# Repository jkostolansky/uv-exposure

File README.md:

UV Exposure
===========

UV Exposure is a controller for a simple UV exposure unit for home PCB etching. It is written in Arduino programming language.

Repository Contents
-------------------

* **/schematics**
    * **/schematics/eagle** - Eagle schematics and PCB layout
    * **/schematics/images** - Images of schematics and PCB layout
* **/uv_exposure** - Arduino source code

The Beer-Ware License
---------------------

Juraj Kostolanský (@jkostolansky) wrote this file. As long as you retain this notice you can do whatever you want with this stuff. If we meet some day, and you think this stuff is worth it, you can buy me a beer in return.

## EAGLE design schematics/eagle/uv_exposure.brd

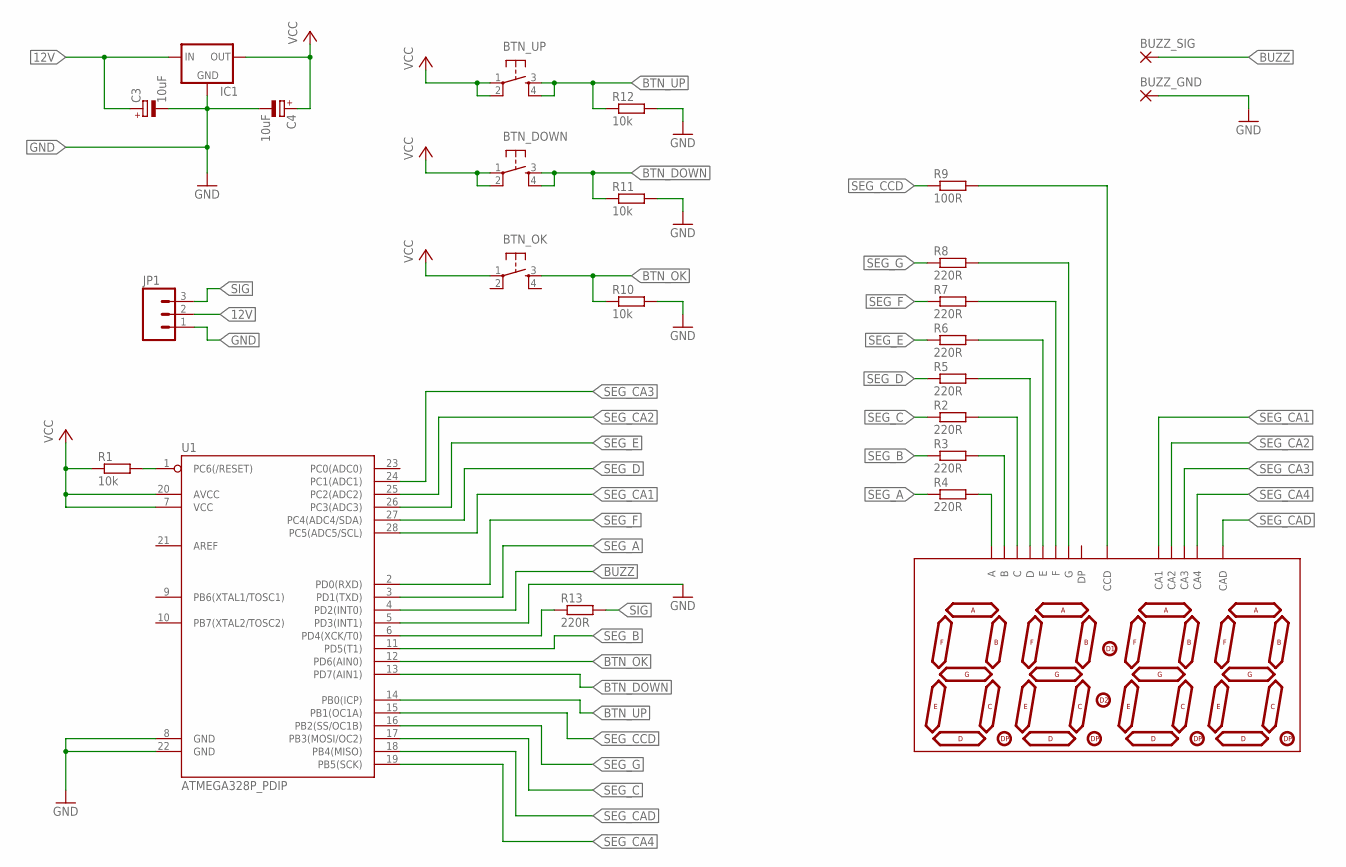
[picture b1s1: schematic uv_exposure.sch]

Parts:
BTN_DOWN: TAC_SWITCHPTH; TACTILE-PTH
BTN_OK: TAC_SWITCHPTH; TACTILE-PTH
BTN_UP: TAC_SWITCHPTH; TACTILE-PTH
BUZZ_GND: 2,54/0,8
BUZZ_SIG: 2,54/0,8
C3, C4: 10uF; E2-5
IC1: V_REG_78XXSINK; TO220-IGO
JP1: M03LOCK; 1X03_LOCK
R1, R10, R11, R12: 10k; 0207/10
R2, R3, R4, R5, R6, R7, R8, R13: 220R; 0207/10
R9: 100R; 0207/10
U1: ATMEGA328P_PDIP; DIL28-3
U$1: 5461BSDIP14; 5461BS

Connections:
12V: C3.+, IC1.IN, JP1.2
BTN_DOWN: BTN_DOWN.3, BTN_DOWN.4, R11.1, U1.13 (PD7(AIN1))
BTN_OK: BTN_OK.3, R10.1, U1.12 (PD6(AIN0))
BTN_UP: BTN_UP.3, BTN_UP.4, R12.1, U1.14 (PB0(ICP))
BUZZ: BUZZ_SIG.1, U1.4 (PD2(INT0))
GND: BUZZ_GND.1, C3.-, C4.-, IC1.GND, JP1.1, R10.2, R11.2, R12.2, U1.5 (PD3(INT1)), U1.8 (GND), U1.22 (GND)
unnamed: R1.2, U1.1 (PC6(/RESET))
unnamed: R4.2, U$1.13 (A)
unnamed: R3.2, U$1.9 (B)
unnamed: R2.2, U$1.4 (C)
unnamed: R5.2, U$1.2 (D)
unnamed: R6.2, U$1.1 (E)
unnamed: R7.2, U$1.12 (F)
unnamed: R8.2, U$1.5 (G)
unnamed: R9.2, U$1.8 (CCD)
unnamed: R13.1, U1.6 (PD4(XCK/T0))
SEG_A: R4.1, U1.3 (PD1(TXD))
SEG_B: R3.1, U1.11 (PD5(T1))
SEG_C: R2.1, U1.17 (PB3(MOSI/OC2))
SEG_CA1: U1.28 (PC5(ADC5/SCL)), U$1.14 (CA1)
SEG_CA2: U1.25 (PC2(ADC2)), U$1.11 (CA2)
SEG_CA3: U1.24 (PC1(ADC1)), U$1.10 (CA3)
SEG_CA4: U1.19 (PB5(SCK)), U$1.6 (CA4)
SEG_CAD: U1.18 (PB4(MISO)), U$1.7 (CAD)
SEG_CCD: R9.1, U1.15 (PB1(OC1A))
SEG_D: R5.1, U1.27 (PC4(ADC4/SDA))
SEG_E: R6.1, U1.26 (PC3(ADC3))
SEG_F: R7.1, U1.2 (PD0(RXD))
SEG_G: R8.1, U1.16 (PB2(SS/OC1B))
SIG: JP1.3, R13.2
VCC: BTN_DOWN.1, BTN_DOWN.2, BTN_OK.1, BTN_UP.1, BTN_UP.2, C4.+, IC1.OUT, R1.1, U1.7 (VCC), U1.20 (AVCC)

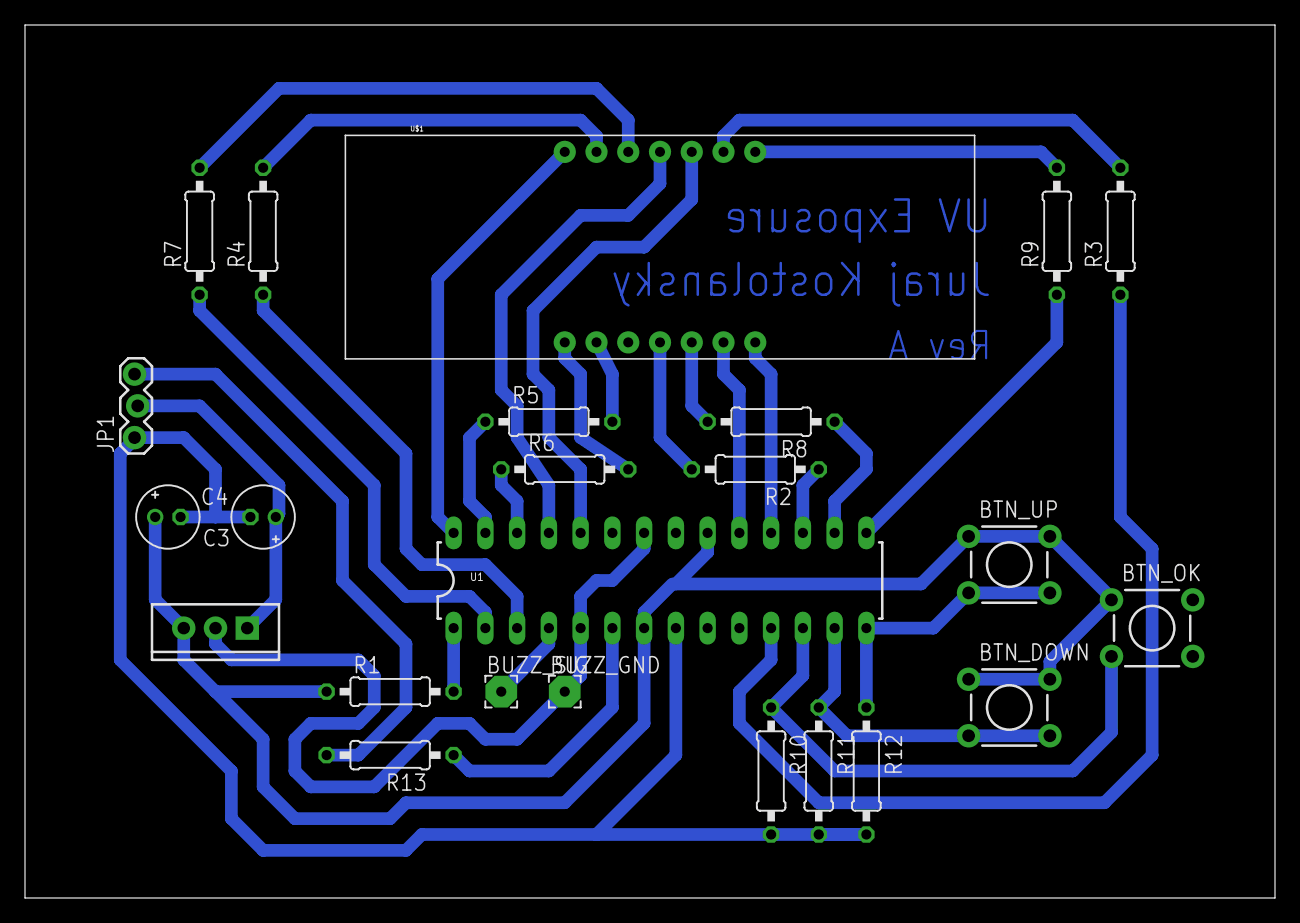
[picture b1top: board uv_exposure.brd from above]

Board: 2 copper layers, 100.0 x 69.8 mm, 24 parts (0 on the bottom side), 31 nets.

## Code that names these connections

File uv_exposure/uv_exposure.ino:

/*
  UV Exposure
  Countdown timer for UV exposure unit.

  by Juraj Kostolansky
*/

// pinout
#define SEG_A          1
#define SEG_B          5
#define SEG_C         11
#define SEG_D         A4
#define SEG_E         A3
#define SEG_F          0
#define SEG_G         10
#define SEG_CCD        9
#define SEG_CA1       A5
#define SEG_CA2       A2
#define SEG_CA3       A1
#define SEG_CA4       13
#define SEG_CAD       12
#define BTN_UP         8
#define BTN_DWN        7
#define BTN_OK         6
#define SIG            4
#define BUZZ           2

// settings
#define BTN_DELAY         500
#define SEG_BLINK_DELAY  1000
#define MODE_SETTINGS       0
#define MODE_COUNTER        1
#define MODE_FINISH         2

// global variables
const int seg_c_seq[7] = { SEG_A, SEG_B, SEG_C, SEG_D, SEG_E, SEG_F, SEG_G };
const int seg_a_seq[7] = { SEG_CA1, SEG_CA2, SEG_CA3, SEG_CA4 };
const byte numbers[10] = { 0b1000000, 0b1111001, 0b0100100, 0b0110000, 0b0011001, 0b0010010, 0b0000010, 0b1111000, 0b0000000, 0b0010000 };

unsigned long timeSet       = 300000;
unsigned long timeStart     = 0;
int           mode          = MODE_SETTINGS;
unsigned long btnDwnEnd     = 0;
unsigned long btnUpEnd      = 0;
unsigned long btnOkEnd      = 0;
unsigned long segEnd        = 0;
boolean       segDisplay    = true;
int           curDigit      = 0;

void setup() {
  // initialize display
  pinMode(SEG_A,   OUTPUT);
  pinMode(SEG_B,   OUTPUT);
  pinMode(SEG_C,   OUTPUT);
  pinMode(SEG_D,   OUTPUT);
  pinMode(SEG_E,   OUTPUT);
  pinMode(SEG_F,   OUTPUT);
  pinMode(SEG_G,   OUTPUT);
  pinMode(SEG_CCD, OUTPUT);
  pinMode(SEG_CA1, OUTPUT);
  pinMode(SEG_CA2, OUTPUT);
  pinMode(SEG_CA3, OUTPUT);
  pinMode(SEG_CA4, OUTPUT);
  pinMode(SEG_CAD, OUTPUT);

  // initialize buttons
  pinMode(BTN_UP, INPUT);
  pinMode(BTN_DWN, INPUT);
  pinMode(BTN_OK, INPUT_PULLUP);

  // initialize buzzer
  pinMode(BUZZ, OUTPUT);

  // initialize signal output
  pinMode(SIG, OUTPUT);
  digitalWrite(SIG, LOW);
}

void loop() {

  /**********************
   *       DISPLAY      *
   **********************/

  switch(mode) {
    case MODE_SETTINGS:
      displayTime(timeSet, false, false);
      break;
    case MODE_COUNTER:
      displayTime(timeSet - (millis() - timeStart), true, false);
      break;
    case MODE_FINISH:
      displayTime(0, true, true);
      break;
  }


  /**********************
   *       COUNTER      *
   **********************/

  if(mode == MODE_COUNTER) {
    if(timeStart == 0)
     timeStart = millis();

    if((millis() - timeStart) < timeSet) {
      digitalWrite(SIG, HIGH);
    } else {
      segEnd = 0;
      mode = MODE_FINISH;
    }
  }

  if(mode == MODE_FINISH) {
    digitalWrite(SIG, LOW);
    timeStart = 0;
  }

  /**********************
   *       CONTROL      *
   **********************/

  if(mode == MODE_SETTINGS) {
    // DOWN button
    if(digitalRead(BTN_DWN) == HIGH) {
      if(millis() > btnDwnEnd) {
        btnDwnEnd = millis() + BTN_DELAY;
        timeSet = adjustDigit(timeSet, curDigit, -1);
      }
    } else {
      btnDwnEnd = 0;
    }

    // UP button
    if(digitalRead(BTN_UP) == HIGH) {
      if(millis() > btnUpEnd) {
        btnUpEnd = millis() + BTN_DELAY;
        timeSet = adjustDigit(timeSet, curDigit, 1);
      }
    } else {
      btnUpEnd = 0;
    }

    // OK button
    if(digitalRead(BTN_OK) == HIGH) {
      if(millis() > btnOkEnd) {
        btnOkEnd = millis() + BTN_DELAY;
        curDigit++;
      }
    } else {
      btnOkEnd = 0;
    }

    if(curDigit >= 4) {
      curDigit = 0;
      mode = MODE_COUNTER;
    }
  }

  if(mode == MODE_COUNTER) {
    // OK button
    if(digitalRead(BTN_OK) == HIGH) {
      if(millis() > btnOkEnd) {
        btnOkEnd = millis() + BTN_DELAY;
        segEnd = 0;
        mode = MODE_FINISH;
      }
    } else {
      btnOkEnd = 0;
    }
  }

  if(mode == MODE_FINISH) {
    // OK button
    if(digitalRead(BTN_OK) == HIGH) {
      if(millis() > btnOkEnd) {
        btnOkEnd = millis() + BTN_DELAY;
        mode = MODE_SETTINGS;
      }
    } else {
      btnOkEnd = 0;
    }
  }
}

unsigned long adjustDigit(unsigned long time, int digit, int adjust) {
  unsigned timeString  = getTimeString(time);

  unsigned before    = (timeString / round(pow(10, 3-digit+1)));
  unsigned oldDigit  = (timeString / round(pow(10, 3-digit))) % 10;
  unsigned after     = (timeString % round(pow(10, 3-digit)));

  unsigned newDigit;
  int digMax = (digit == 2 ? 5 : 9);
  if(adjust == 1) {
    newDigit = (oldDigit+1) % (digMax+1);
  } else {
    if(oldDigit == 0)
      newDigit = digMax;
    else
      newDigit = oldDigit-1;
  }

  unsigned adjusted = (before * round(pow(10, 3-digit+1))) + (newDigit * round(pow(10, 3-digit))) + after;
  return getTimeFromString(adjusted);
}

void displayTime(unsigned long time, boolean blinkColon, boolean blinkDisplay) {
  if(blinkDisplay) {
   if(segEnd == 0)
     segEnd = millis();
   if(millis() > segEnd) {
     segEnd += SEG_BLINK_DELAY;
     segDisplay = !segDisplay;
   }
  }

  unsigned timeString  = getTimeString(time);
  for(int digit = 0; digit < 4; digit++) {
    int number = (timeString / round(pow(10, 3-digit)) ) % 10;
    // ON
    if(!blinkDisplay || segDisplay) {
      digitalWrite(seg_a_seq[digit], HIGH);
      if(!blinkColon || (timeString % 2 == 0)) {
        digitalWrite(SEG_CAD, HIGH);
        digitalWrite(SEG_CCD, LOW);
      }
      for (int i = 0; i < 7; i++)
        digitalWrite(seg_c_seq[i], bitRead(numbers[number], i));
    }
    // wait
    delay(2);
    // OFF
    digitalWrite(seg_a_seq[digit], LOW);
    digitalWrite(SEG_CAD, LOW);
    digitalWrite(SEG_CCD, HIGH);
    for (int i = 0; i < 7; i++)
      digitalWrite(seg_c_seq[i], HIGH);
  }
}

unsigned getTimeString(unsigned long time) {
  unsigned timeSeconds = (time/1000) % 60;
  unsigned timeMinutes = ((time/1000) - timeSeconds) / 60;
  return timeMinutes * 100 + timeSeconds;
}

unsigned long getTimeFromString(unsigned string) {
  unsigned long timeSeconds = (unsigned long)string % 100;
  unsigned long timeMinutes = ((unsigned long)string - timeSeconds) / 100;
  return (timeMinutes*60 + timeSeconds) * 1000;
}

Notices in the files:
parts and their libraries:
SparkFun-DigitalIC: Licensing: Creative Commons ShareAlike 4.0 International - https://creativecommons.org/licenses/by-sa/4.0
